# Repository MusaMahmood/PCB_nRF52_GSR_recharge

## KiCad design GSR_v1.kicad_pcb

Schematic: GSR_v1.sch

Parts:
A1: CHIP-ANT
C1, C9, C10, C14, C15: 10uF; C_0402
C2: 22uF; C_0402
C3, C4, C5, C26, C33: 100nF; C_0402
C6, C7, C8, C11: 0.1uF; C_0402
C16, C17: 4.7uF; C_0402
C18: 1.0uF; C_0402
C21: 4.7µF; C_0402
C22: 100nF; C_0603
C23: 1.0µF; C_0603
C24, C25, C28, C29: 12pF; C_0402
C27: N.C.
C30: 1.0pF; C_0402
C34: 100pF; C_0402
D1, D3: LED; LED_0603
D4: D_Schottky; LED_0603
F1: 2450FM07A0029
IC1: AD5242BRUZ1M; SOP65P640X120-16N; Mouser Part Number 584-AD5242BRUZ1M
J1: Micro_SD_Card_Det
L1: 2.20µH; L_0603
L2: 4.7uH; L_0603
L3: 15nH; L_0402
L4: 10uH; L_0603
L5: 2.7nH; L_0402
L6: 3.9nH; L_0402
P1, P2, P3, P4: CONN_2; Pin_Header_Straight_1x02_Pitch2.54mm
Q1: DMP21D5UFB4-7B; X2-DFN1006
R1, R2, R4, R16, R17, R18, R19: 4.7k; R_0402
R3, R6, R13, R14: 200k; R_0402
R5, R7, R15: 1M; R_0402
R8: N.C.; R_0402
R9: 2k; R_0402
R10, R11, R12: 100k; R_0402
R20: 1k; R_0402
S1: SSAJ120100; Mouser Part Number 688-SSAJ120100
U1: TPS63001
U2: LM324N
U3: NRF528XX-QFAA; UQFN-48-1EP_6x6mm_Pitch0.4mm
U4: TMP116
U5: TPS2294x
U6: MCP73831; DFN-8-1EP_2x3mm_Pitch0.5mm
U7: ADS1220; QFN-16-1EP_3x3mm_P0.5mm_EP1.8x1.8mm
U8: TPS61222; SOT-363_SC-70-6
U9: 4050; SOIC127P600X175-16N
X1: Crystal_GND24; Crystal_SMD_2016-4pin_2.0x1.6mm
X2: 32.768 kHz; Crystal_SMD_2012-2pin_2.0x1.2mm

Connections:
5V_in_charge: C16.1, D4.2, P3.1, Q1.1, R10.1, U6.1 (Vdd), U6.2 (Vdd)
/AD5242_SCL: IC1.7, R19.1, U3.21 (P0.18/TD[0]/SWO)
/AD5242_SDA: IC1.8, R4.1, U3.20 (P0.17)
/ADC_AIN0: C5.2, R15.1, U7.9
/AIN_BAT_DIV_VOLTAGE: R5.1, R7.2, U3.6 (P0.04/AIN2)
/BATT_IN: C17.1, P1.1, Q1.2, U6.3 (Vbat), U6.4 (Vbat)
/CMD_MOSI: U3.28 (P0.23), U9.3
/DAT0_MISO: J1.7, U3.24 (P0.21/nRESET)
/DAT1_UNUSED: J1.8
/DAT2_UNUSED: J1.1
/DAT3_CS: R20.1, U3.29 (P0.24), U9.9
/DEC1: C26.1, U3.1 (DEC1)
/DEC2: C27.1, U3.32 (DEC2)
/DEC3: C34.1, U3.33 (DEC3)
/DIN: U3.16 (P0.13), U7.14
/DOUT: U3.17 (P0.14/TRACEDATA[3]), U7.13
/ELECTRODE_INPUT: IC1.3, P4.1, U2.5 (+)
/LOAD_IN: C15.1, C18.2, D4.1, Q1.3, R8.2, S1.1, U5.5 (Vin)
/LOAD_SW_CTRL: U3.5 (P0.03/AIN1), U5.4 (ON)
/RF: C30.1, F1.4 (OUT)
/RT_1: C3.2, IC1.2, R1.1, R2.2, R3.2
/SPI_SCLK: U3.15 (P0.12), U7.15
/SPI_~CS: U3.14 (P0.11), U7.16
/SWDCLK: P2.1, U3.25 (SWDCLK)
/SWDIO: P2.2 (PM), U3.26 (SWDIO)
/TMP_ALERT: R18.1, U4.3 (ALERT)
/TMP_SCL: R17.1, U3.22 (P0.19), U4.1 (SCL)
/TMP_SDA: R16.1, U3.23 (P0.20/TRACECLK), U4.6 (SDA)
/uSD_CLK: U3.27 (P0.22), U9.5, U9.7
/~DRDY: U3.18 (P0.15/TD[2]), U7.12
AVDD: C8.1, C10.1, U7.10, U8.2, U8.4
DGND: C1.2, C2.2, C3.1, C4.2, C5.1, C6.1, C7.2, C8.2, C9.2, C10.2, C11.2, C14.2, C15.2, C16.2, C17.2, C18.1, C21.1, C22.2, C23.2, C24.1, C25.1, C26.2, C27.2, C28.2, C29.2, C33.1, C34.2, F1.1 (GND), F1.3 (GND), IC1.4, IC1.9, IC1.10, IC1.11, IC1.12, J1.6, J1.9, J1.10, J1.11, L5.2, P1.2 (PM), P3.2 (PM), P4.2 (PM), R2.1, R6.1, R7.1, R9.2, R10.2, R13.2, S1.4, S1.5, U1.3 (PGND), U1.9 (GND), U1.11 (THERMAL), U2.11 (V-), U3.31 (VSS), U3.45 (VSS), U3.49 (THERMAL), U4.2 (GND), U4.4 (ADD0), U4.7 (THRM), U5.2 (GND), U6.6 (Vss), U6.9 (EP_THRM), U7.1, U7.2, U7.3, U7.8, U7.17, U8.3, U9.8, U9.11, U9.14, X1.2, X1.4
DVDD: C2.1, C4.1, C6.2, C7.1, C11.1, C21.2, C22.1, C33.2, D3.2 (A), IC1.5, IC1.6, J1.4, R1.2, R4.2, R16.2, R17.2, R18.2, R19.2, U1.1 (VOUT), U1.10 (FB), U2.4 (V+), U3.13 (VDD), U3.36 (VDD), U3.48 (VDD), U4.5 (V+), U7.11, U9.1
unnamed: A1.1 (ANT), L6.2
unnamed: C14.1, R5.2, U5.1 (Vout)
unnamed: C23.1, L3.2, U3.46 (DEC4)
unnamed: C24.2, U3.34 (XC1), X1.1
unnamed: C25.2, U3.35 (XC2), X1.3
unnamed: C28.1, U3.2 (P0.00/XL1), X2.2
unnamed: C29.1, U3.3 (P0.01/XL2), X2.1
unnamed: C30.2, L5.1, L6.1
unnamed: D1.1 (K), R20.2
unnamed: D1.2 (A), U9.6
unnamed: D3.1 (K), U6.5 (STAT)
unnamed: F1.2 (IN), U3.30 (ANT)
unnamed: J1.2, U9.10
unnamed: J1.3, U9.2
unnamed: J1.5, U9.4
unnamed: L1.1, U1.4 (L1)
unnamed: L1.2, U1.2 (L2)
unnamed: L2.1, U8.5
unnamed: L3.1, L4.2
unnamed: L4.1, U3.47 (DCC)
unnamed: R3.1, R6.2, U2.3 (+)
unnamed: R8.1, U5.3 (OC)
unnamed: R9.1, U6.8 (PROG)
unnamed: R11.1, U2.1, U2.2 (-)
unnamed: R11.2, R14.1, U2.9 (-)
unnamed: R12.1, U2.6 (-), U2.7
unnamed: R12.2, R13.1, U2.10 (+)
unnamed: R14.2, R15.2, U2.8
VCC: C1.1, C9.1, L2.2, S1.3, U1.5 (VIN), U1.6 (EN), U1.7 (PS/SYNC), U1.8 (VINA), U8.1, U8.6

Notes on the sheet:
This network will need to be tuned
No reverse polarity protection; use caution and do not connect battery and debugger at same time!
Power Regulation Circuitry
Vcc = Raw battery signal
Vout
TPS22941
MAY DISCONNECT OUTPUT OC PIN!!! HIGH VOLTAGE MAY DMG NRF CHIP. REMOVE R8 ON PCB;
Load Sharing Circuit
Q1 = DMP21D5UFB4 P-mosfet Footprint: X2-DFN1006-3
D4 = SMD Schottky Diode (0603)
TO LOAD
R9 sets current limit NOTE: STAT PIN IS 5V
GSR Analog Front End (Using 4-Op Amp LM324-N Configured as Instrumentation Amp)
Temperature Sensor IC
nRF52 Module
LOAD_IN = Vcc = Battery Voltage
Recharge Circuitry
Load Switch for Battery Measurement with Voltage Divider (V/2)
3.3V Voltage Regulator, 2A Max output
Pin Headers and General Connection Labeling
MicroSD Card
5.0 V Regulator
reference
ADC
Digital Potentiometer
Switch
Use 16-Pin SOIC Package

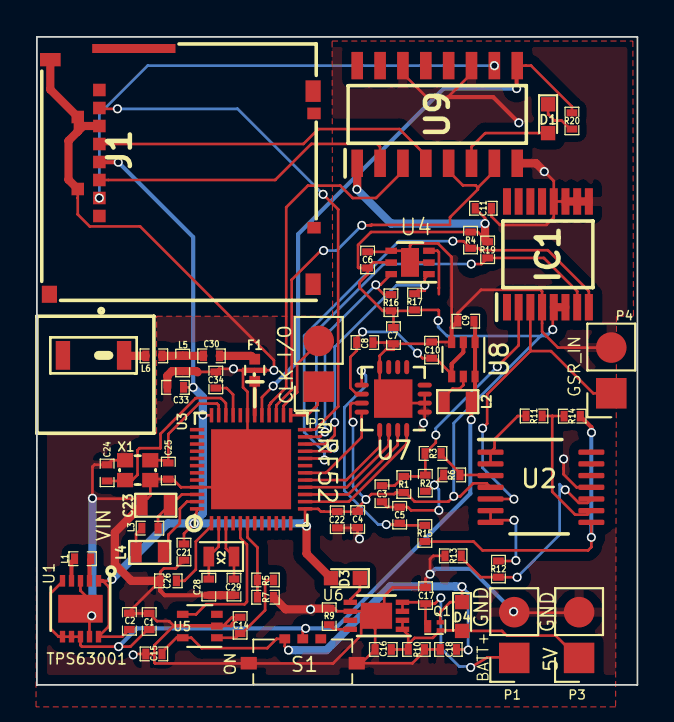
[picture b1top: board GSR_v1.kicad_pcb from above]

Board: 2 copper layers, 33.4 x 36.0 mm, 75 parts (0 on the bottom side), 57 nets.

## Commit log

2018-08-30 Initial commit. Design incomplete.
2018-08-31 Upgraded to KiCAD 5.0 compat
2018-08-31 Updated footprint for LM324
2018-08-31 Nathan edits and my finalization to PCB design.
2018-09-02 Fixed missing connections, resolved issues.
2018-09-04 Major refactoring and cleanup.
2018-09-04 Updated Gerbers, deleted old gerber files, minor details. Updated silkscreen (back)
2018-09-04 Fixed F.Silk to show orientation of TSSOP.
2018-09-17 Update .gitignore, updated missing libraries.
2019-01-09 moved connectors for Temp sensor down to make space for uSD card
2019-01-09 Added microSD Card to sch and pcb
2019-01-09 Added ground plane under micoSD slot
2019-01-09 Slight tweaking, set fills to DGND.
2019-01-09 Updated Gerber files, fixed back silkscreen
2019-01-11 Replaced through-hole footprints with pads.
2019-03-13 Updated schematic, and footprints. PCB needs arrangement and routing.
2019-03-14 Added switch and arranged and routed PCB.
2019-03-28 Fixed routing of AD5242.
2019-03-28 Fixed SHDN pin to VDD.
2019-04-01 Fixed footprint for ADS1220.
2019-04-19 Finalized digital potentiometer ADC.
2019-05-02 Updated digital potentiometer ADC
2019-05-02 Updated schematic with new hex buffers for driving uSD Card.
2019-05-02 Update bottom solder mask, and gerber files.
